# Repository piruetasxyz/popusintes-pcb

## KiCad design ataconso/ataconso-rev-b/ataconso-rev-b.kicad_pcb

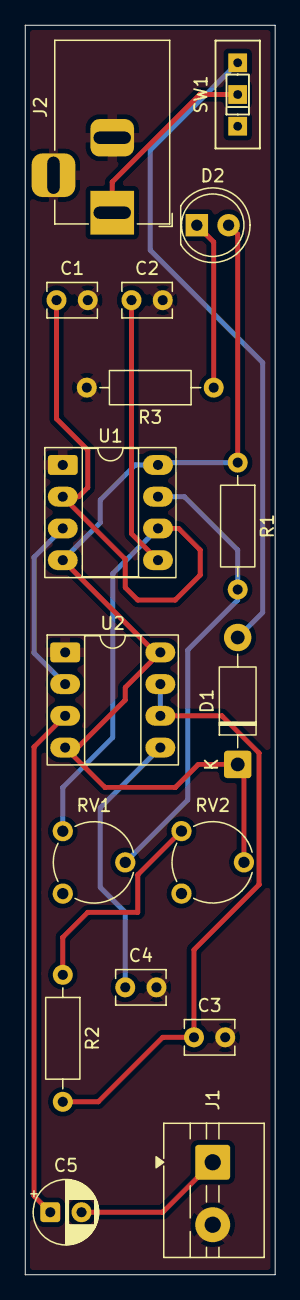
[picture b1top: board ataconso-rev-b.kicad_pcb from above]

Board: 2 copper layers, 20.0 x 100.0 mm, 17 parts (0 on the bottom side), 14 nets.

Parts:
C1: 10n; C_Disc_D3.8mm_W2.6mm_P2.50mm
C2, C3, C4: 100n; C_Disc_D3.8mm_W2.6mm_P2.50mm
C5: 100u; CP_Radial_D5.0mm_P2.50mm
D1: 1n4007; D_DO-41_SOD81_P10.16mm_Horizontal
D2: LED; LED_D5.0mm
J1: Screw_Terminal_01x02; TerminalBlock_MaiXu_MX126-5.0-02P_1x02_P5.00mm
J2: Barrel_Jack_Switch; BarrelJack_Horizontal
R1: 10k; R_Axial_DIN0207_L6.3mm_D2.5mm_P10.16mm_Horizontal
R2, R3: 1k; R_Axial_DIN0207_L6.3mm_D2.5mm_P10.16mm_Horizontal
RV1, RV2: 470k; Potentiometer_Piher_PT-6-V_Vertical
SW1: SW_SPDT; spdt_ssd12d00g3
U1, U2: NE555D; DIP-8_W7.62mm_Socket_LongPads

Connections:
GND: C1.2, C2.2, C3.2, C4.2, J1.2, J2.2, J2.3, R3.2, U1.1 (GND), U2.1 (GND)
unnamed: D1.2 (A), SW1.3 (C)
unnamed: D2.1 (K), R3.1
unnamed: C5.2, J1.1
unnamed: R2.1, RV2.3
unnamed: J2.1, SW1.2 (B)
unnamed: C2.1, U1.5 (CONT)
unnamed: R1.2, RV1.2, U1.7 (DISCH)
unnamed: U1.3 (OUT), U2.2 (TRIG)
unnamed: C1.1, RV1.3, U1.2 (TRIG), U1.6 (THRES)
unnamed: C4.1, U2.5 (CONT)
unnamed: C3.1, R2.2, U2.6 (THRES), U2.7 (DISCH)
unnamed: C5.1, U2.3 (OUT)
VCC: D1.1 (K), D2.2 (A), R1.1, RV2.2, U1.4 (~RST), U1.8 (VCC), U2.4 (~RST), U2.8 (VCC)
